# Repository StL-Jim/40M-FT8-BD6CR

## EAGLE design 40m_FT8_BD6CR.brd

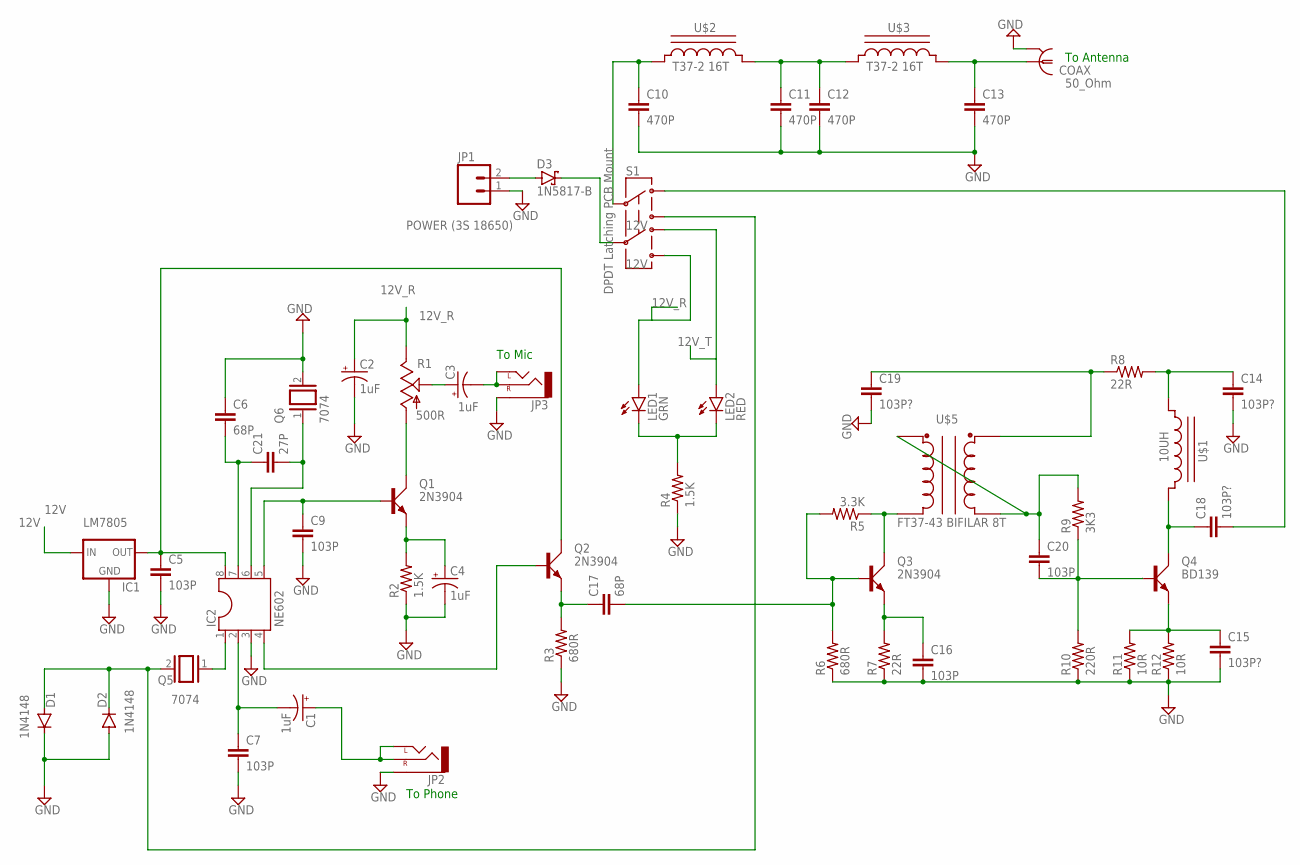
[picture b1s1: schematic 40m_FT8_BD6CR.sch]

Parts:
C1, C2, C3, C4: 1uF; E2-4
C5, C7, C9, C16, C20: 103P; C050-025X075
C6, C17: 68P; C050-025X075
C10, C11, C12, C13: 470P; C050-025X075
C14, C15, C18, C19: 103P?; C050-025X075
C21: 27P; C050-025X075
COAX: 50_Ohm; R141426
D1, D2: 1N4148; DO35-10
D3: 1N5817-B; DO41-7.6
IC1: LM7805; 78XXL
IC2: NE602; DIL08
JP1: POWER (3S 18650); JST-2-PTH-NS
JP2, JP3: AUDIO-JACKPTH; AUDIO-JACK
LED1: GRN; LED_5MM
LED2: RED; LED_5MM
Q1, Q2, Q3: 2N3904; TO92D
Q4: BD139; TO92D
Q5, Q6: 7074; QS
R1: 500R; CT6
R2, R4: 1.5K; 0207/10
R3, R6: 680R; 0207/10
R5: 3.3K; 0207/10
R7, R8: 22R; 0207/10
R9: 3K3; 0207/10
R10: 220R; 0207/10
R11, R12: 10R; 0207/10
S1: DPDT Latching PCB Mount; AYZ0202
U$1: 10uH; T37_INDUCTOR
U$2: T37-2 16T; T37_INDUCTOR
U$3: T37_INDUCTOR_FLAT; T37_INDUCTOR
U$5: FT37-43 BIFILAR 8T; T37_TRANSFORMER

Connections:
12V: D3.C, IC1.IN, S1.5
12V_R: C2.+, LED1.A, R1.E, S1.6
12V_T: LED2.A, S1.4
GND: C2.-, C4.-, C5.2, C6.1, C7.2, C9.2, C10.2, C11.2, C12.2, C13.2, C14.2, C15.2, C16.2, C19.2, COAX.2, COAX.3 (2), COAX.4 (2), COAX.5 (2), D1.C, D2.A, IC1.GND, IC2.3, JP1.1, JP2.SLEEVE, JP3.SLEEVE, Q6.2, R2.1, R3.1, R4.1, R6.1, R7.1, R10.1, R11.1, R12.1
unnamed: C3.+, R1.S
unnamed: C5.1, IC1.OUT, IC2.8, Q2.C
unnamed: C13.1, COAX.1, U$3.CA
unnamed: C11.1, C12.1, U$2.CA, U$3.CB
unnamed: C10.1, S1.2, U$2.CB
unnamed: D3.A, JP1.2
unnamed: C3.-, JP3.RING (RIGHT), JP3.TIP (LEFT)
unnamed: C18.1, Q4.C, U$1.CA
unnamed: C14.1, R8.2, U$1.CB
unnamed: C19.1, R8.1, U$5.C2B
unnamed: C20.1, R9.2, U$5.C1B, U$5.C2A
unnamed: C20.2, Q4.B, R9.1, R10.2
unnamed: LED1.K (C), LED2.K (C), R4.2
unnamed: Q3.C, R5.1, U$5.C1A
unnamed: C17.2, Q3.B, R5.2, R6.2
unnamed: C16.1, Q3.E, R7.2
unnamed: C17.1, Q2.E, R3.2
unnamed: C9.1, IC2.5, Q1.B
unnamed: Q1.C, R1.A
unnamed: IC2.1, Q5.1
unnamed: C6.2, C21.1, IC2.7
unnamed: C21.2, IC2.6, Q6.1
unnamed: D1.A, D2.C, Q5.2, S1.3
unnamed: C1.+, JP2.RING (RIGHT), JP2.TIP (LEFT)
unnamed: C1.-, C7.1, IC2.2
unnamed: C4.+, Q1.E, R2.2
unnamed: IC2.4, Q2.B
unnamed: C18.2, S1.1
unnamed: C15.1, Q4.E, R11.2, R12.2

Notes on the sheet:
To Phone
To Antenna
To Mic

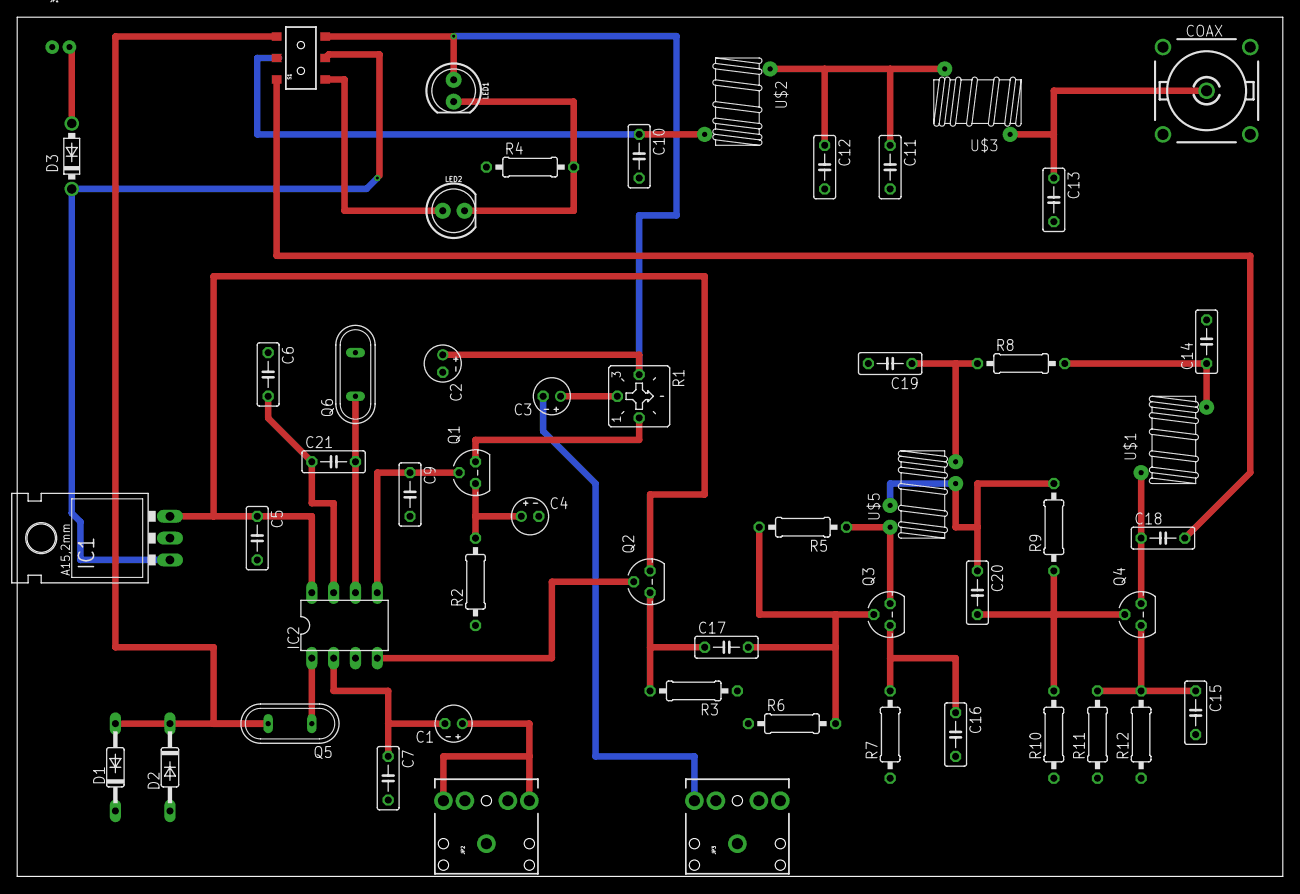
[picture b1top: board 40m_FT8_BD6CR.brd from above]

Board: 2 copper layers, 147.3 x 100.0 mm, 54 parts (0 on the bottom side), 33 nets.

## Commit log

2019-03-27 Initial commit of schematic files.
    This is a very early commit of the schematic files.
    Changes to be committed:
    new file: 40m_FT8_BD6CR.s#1
    new file: 40m_FT8_BD6CR.sch
    new file: eagle.epf
2019-03-27 First version done and ready for review
    Changes to be committed:
    new file: 40m_FT8_BD6CR.pdf
    modified: 40m_FT8_BD6CR.s#1
    new file: 40m_FT8_BD6CR.s#2
    new file: 40m_FT8_BD6CR.s#3
    new file: 40m_FT8_BD6CR.s#4
2019-03-29 Updated schematic and added the board layout
    Updated schematic and added the board layout
    1. I found I was missing a resistor (R7 22R)
    2. I removed all the audio/mic jacks and replaced them with JST-XH 2 pin connectors so the audio/mic jacks can be connected to a case of some sort.
2019-04-28 updated with vias.
    Still some work to do on vias and routing
2019-05-15 Ready for version 1 review
    Ready for version 1 review. Added vias and finished traces on the
    bottom side of the board.

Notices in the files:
parts and their libraries:
SparkFun-PowerIC: Licensing: Creative Commons ShareAlike 4.0 International - https://creativecommons.org/licenses/by-sa/4.0
